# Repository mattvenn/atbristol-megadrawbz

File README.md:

# @bristol energy drawing robot

## updates

* [youtube playlist](https://www.youtube.com/playlist?list=PLmcDgdDpcaPiOdnMplbk7o1K5Kpvp_UAL)
* [photos](https://goo.gl/photos/KGhmjEyrZScbemvW7)

## details

### hardware

* [Beagle bone breakout board](hardware/bbbbbb_pcb/)
* [Pen holder](hardware/gondola_pcb/)
* [notes on stepper choice](tests/stepper-choice)

### machinekit/linuxcnc configuration

* Robot is controlled with machinekit running on a beaglebone black.
* Pen holder is controlled via Xbee radio and uses a [custom component] that runs in its own realtime thread.

* [configuration](https://github.com/mattvenn/machinekit-bipod)

### firmware

* [pen holder firmware](firmware/gondola/)

### tests

* [prototypes, tests, proof of concepts](tests)

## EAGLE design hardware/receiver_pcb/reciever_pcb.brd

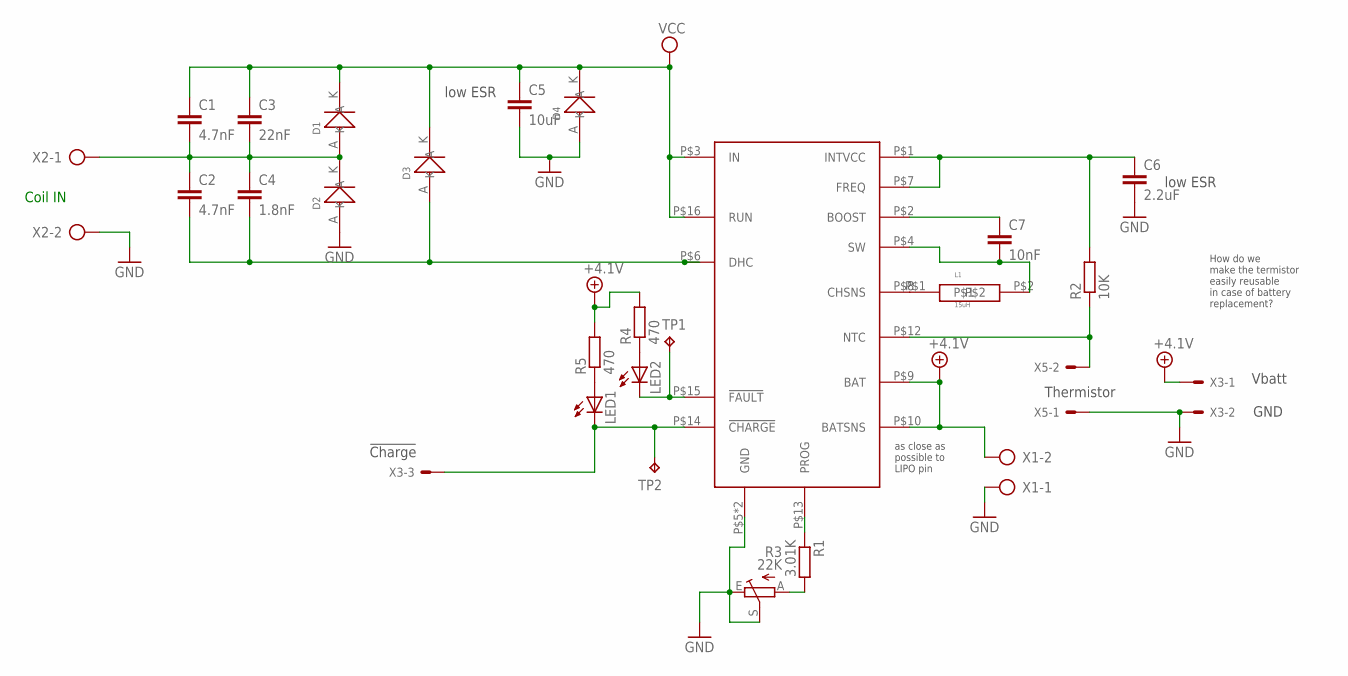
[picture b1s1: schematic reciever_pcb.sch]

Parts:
C1, C2: 4.7nF; C0805
C3: 22nF; C0805
C4: 1.8nF; C0805
C5: 10uF; C0805
C6: 2.2uF; C0805
C7: 10nF; C0805
D1, D2, D3: DFLS240L; POWERDI123
D4: 39VZ; POWERDI123
L1: 15uH; D62LCB
LED1, LED2: LEDCHIP-LED0805; CHIP-LED0805
R1: 3.01K; R0805
R2: 10K; R0805
R3: 22K; S63S
R4, R5: 470; R0805
TP1, TP2: TPTP19R; TP19R
U$1: LT4120; QFN16
X1, X2: AK500/2
X3: KK-156-3
X5: KK-156-2

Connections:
+4.1V: R4.2, R5.2, U$1.P$9 (BAT), U$1.P$10 (BATSNS), X1.2, X3.1
GND: C5.2, C6.2, D2.A, D4.A, R3.E, R3.S, U$1.P$5 (GND), U$1.P$17 (GND), X1.1, X2.2, X3.2, X5.1
unnamed: C1.2, C2.1, C3.2, C4.1, D1.A, D2.K, X2.1
unnamed: C2.2, C4.2, D3.A, U$1.P$6 (DHC)
unnamed: C6.1, R2.2, U$1.P$1 (INTVCC), U$1.P$7 (FREQ)
unnamed: C7.1, U$1.P$2 (BOOST)
unnamed: C7.2, L1.P$2, U$1.P$4 (SW)
unnamed: L1.P$1, U$1.P$8 (CHSNS)
unnamed: R1.1, U$1.P$13 (PROG)
unnamed: R2.1, U$1.P$12 (NTC), X5.2
unnamed: LED1.C, TP2.TP, U$1.P$14 (!CHARGE), X3.3
unnamed: LED2.A, R4.1
unnamed: LED1.A, R5.1
unnamed: R1.2, R3.A
unnamed: LED2.C, TP1.TP, U$1.P$15 (!FAULT)
VCC: C1.1, C3.1, C5.1, D1.K, D3.K, D4.K, U$1.P$3 (IN), U$1.P$16 (RUN)

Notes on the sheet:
Coil IN
low ESR
as close as possible to LIPO pin
How do we make the termistor easily reusable in case of battery replacement?
!Charge
Vbatt
GND
Thermistor

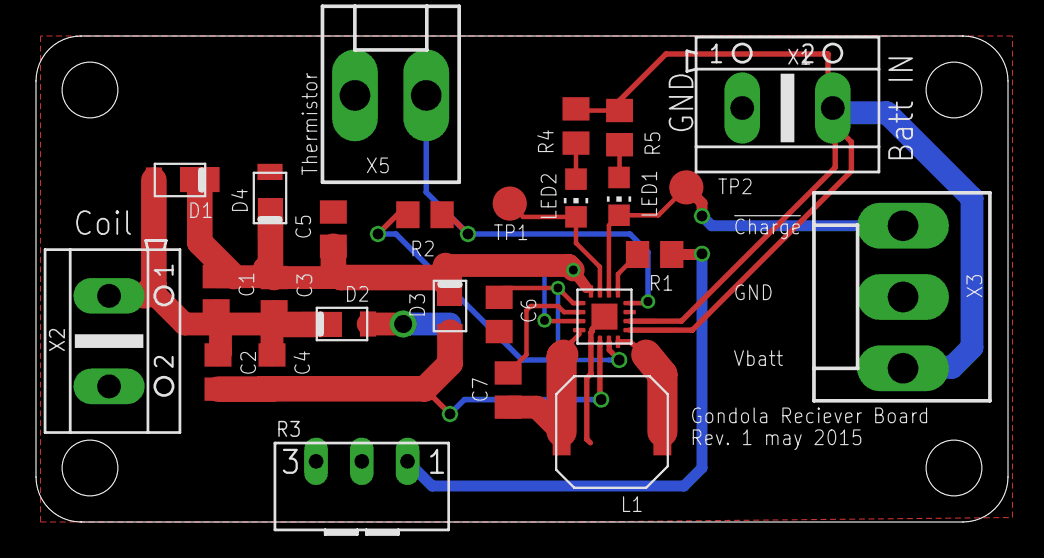
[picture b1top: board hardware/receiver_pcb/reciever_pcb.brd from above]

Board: 2 copper layers, 54.0 x 27.0 mm, 26 parts (0 on the bottom side), 16 nets.

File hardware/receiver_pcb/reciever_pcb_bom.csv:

Part,Value,Device,Package,Description,RS code,Link
C1,4.7nF,C-EUC0805,C0805,"CAPACITOR, European symbol",,
C2,4.7nF,C-EUC0805,C0805,"CAPACITOR, European symbol",,
C3,22nF,C-EUC0805,C0805,"CAPACITOR, European symbol",,
C4,1.8nF,C-EUC0805,C0805,"CAPACITOR, European symbol",,
C5,10uF,C-EUC0805,C0805,"CAPACITOR, European symbol",,
C6,2.2uF,C-EUC0805,C0805,"CAPACITOR, European symbol",,
C7,10nF,C-EUC0805,C0805,"CAPACITOR, European symbol",,
D1,DFLS240L,DFLS240L,POWERDI123,,,
D2,DFLS240L,DFLS240L,POWERDI123,,,
D3,DFLS240L,DFLS240L,POWERDI123,,,
D4,39VZ,DFLS240L,POWERDI123,,822-2497,http://uk.rs-online.com/web/p/zener-diodes/8222497/
L1,15uH,L-EUL1812,L1812,Toko coil,7521327,http://uk.rs-online.com/web/p/wire-wound-surface-mount-induc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
LED1,,LEDCHIP-LED0805,CHIP-LED0805,LED,,
LED2,,LEDCHIP-LED0805,CHIP-LED0805,LED,,
R1,3.01K,R-EU_R0805,R0805,"RESISTOR, European symbol",,
R2,10K,R-EU_R0805,R0805,"RESISTOR, European symbol",,
R4,470,R-EU_R0805,R0805,"RESISTOR, European symbol",,
R5,470,R-EU_R0805,R0805,"RESISTOR, European symbol",,
TP1,TPTP19R,TPTP19R,TP19R,Test pad,,
TP2,TPTP19R,TPTP19R,TP19R,Test pad,,
U$1,LT4120,LT4120,QFN16,,,
X1,,AK500/2,AK500/2,CONNECTOR,,
X2,,AK500/2,AK500/2,CONNECTOR,,
X3,,KK-156-3,KK-156-3,KK 156 HEADER,,
X4,,AK500/2,AK500/2,CONNECTOR,,

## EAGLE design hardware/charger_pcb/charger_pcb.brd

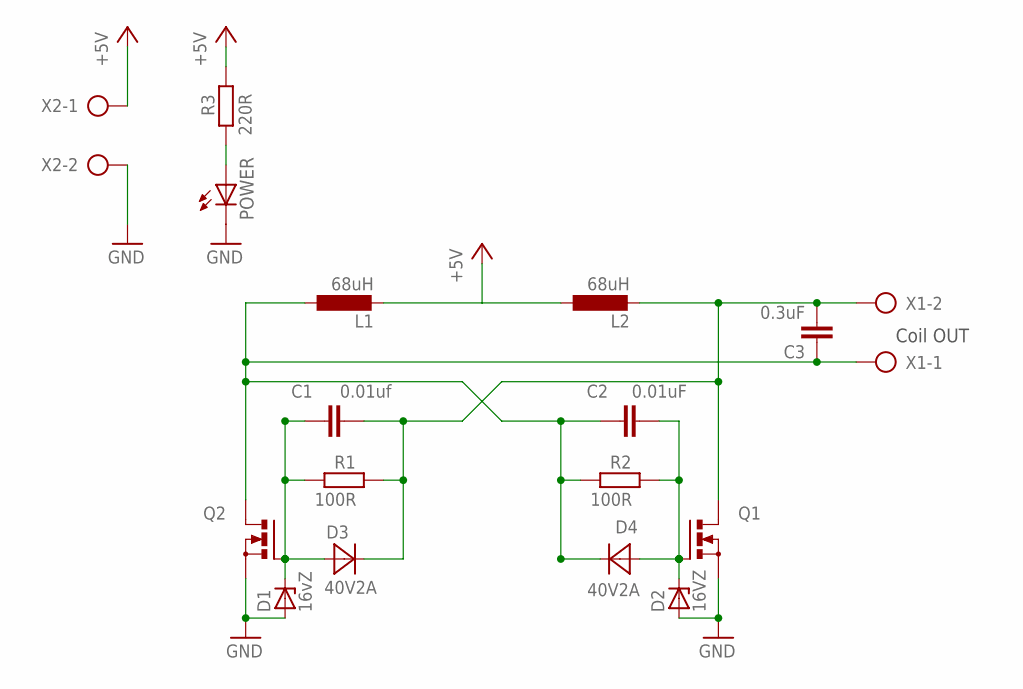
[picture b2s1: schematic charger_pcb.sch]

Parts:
C1: 0.01uf; C0805
C2: 0.01uF; C0805
C3: 0.3uF; C0805
D1: 16vZ; SOD80C
D2: 16VZ; SOD80C
D3, D4: 40V2A; SMA
L1, L2: 68uH; L5650M
POWER: LEDCHIP-LED0805; CHIP-LED0805
Q1, Q2: N-MOSFET-SO8S; SO-08
R1, R2: 100R; R0805
R3: 220R; R0805
X1, X2: AK500/2

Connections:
+5V: L1.2, L2.1, R3.2, X2.1
GND: D1.A, D2.A, POWER.C, Q1.1 (S), Q1.2 (S), Q1.3 (S), Q2.1 (S), Q2.2 (S), Q2.3 (S), X2.2
unnamed: C1.1, D1.C, D3.A, Q2.4 (G), R1.1
unnamed: C2.2, D2.C, D4.A, Q1.4 (G), R2.2
unnamed: POWER.A, R3.1
OUT1: C1.2, C3.2, D3.C, L2.2, Q1.5 (D), Q1.6 (D), Q1.7 (D), Q1.8 (D), R1.2, X1.2
OUT2: C2.1, C3.1, D4.C, L1.1, Q2.5 (D), Q2.6 (D), Q2.7 (D), Q2.8 (D), R2.1, X1.1

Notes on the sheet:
Coil OUT

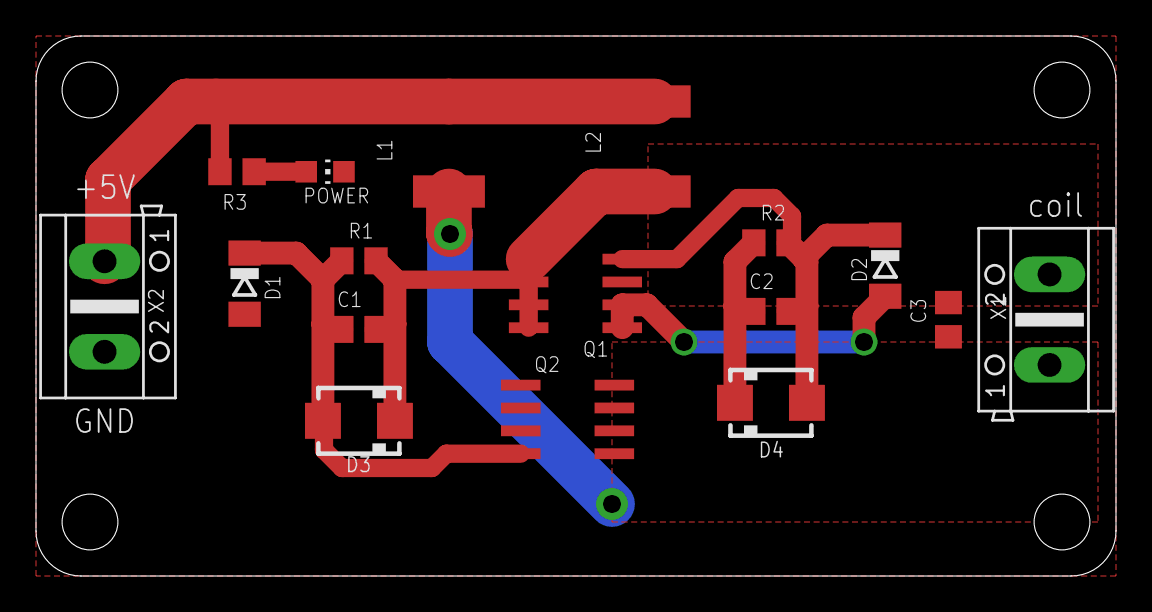
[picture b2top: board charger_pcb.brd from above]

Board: 2 copper layers, 60.0 x 30.0 mm, 17 parts (0 on the bottom side), 7 nets.

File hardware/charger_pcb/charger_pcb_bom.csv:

Qty,Value,Device,Package,Parts,Description,RS code,Link
2,,AK500/2,AK500/2,"X1, X2",CONNECTOR,2204260,http://uk.rs-online.com/web/p/pcb-terminal-blocks/2204260/
1,,LEDCHIP-LED0805,CHIP-LED0805,POWER,LED,8886057,http://uk.rs-online.com/web/p/visible-leds/8886057/
2,,N-MOSFET-SO8S,SO-08,"Q1, Q2",N-Channel MOSFET,915-4960,http://uk.rs-online.com/web/p/mosfet-transistors/9154960/
1,0.01uF,C-EUC0805,C0805,C2,"CAPACITOR, European symbol",4614013,http://uk.rs-online.com/web/p/ceramic-multilayer-capacitors/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
1,0.01uf,C-EUC0805,C0805,C1,"CAPACITOR, European symbol",4614013,http://uk.rs-online.com/web/p/ceramic-multilayer-capacitors/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
1,0.3uF,C-EUC0805,C0805,C3,"CAPACITOR, European symbol",,
2,100R,R-EU_R0805,R0805,"R1, R2","RESISTOR, European symbol",,
1,16VZ,ZENER-DIODESOD80C,SOD80C,D2,Z-Diode,7598775,http://uk.rs-online.com/web/p/zener-diodes/7598775/
1,16vZ,ZENER-DIODESOD80C,SOD80C,D1,Z-Diode,7598775,http://uk.rs-online.com/web/p/zener-diodes/7598775/
1,220R,R-EU_R0805,R0805,R3,"RESISTOR, European symbol",,
2,40V2A,MBRA340T3,SMA,"D3, D4",Surface Mount Schottky Power Rectifier,708-2337,http://uk.rs-online.com/web/p/rectifier-schottky-diodes/7082337/
2,68uH,L-EUL5650M,L5650M,"L1, L2","INDUCTOR, European symbol",6924930,http://uk.rs-online.com/web/p/wire-wound-surface-mount-induc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

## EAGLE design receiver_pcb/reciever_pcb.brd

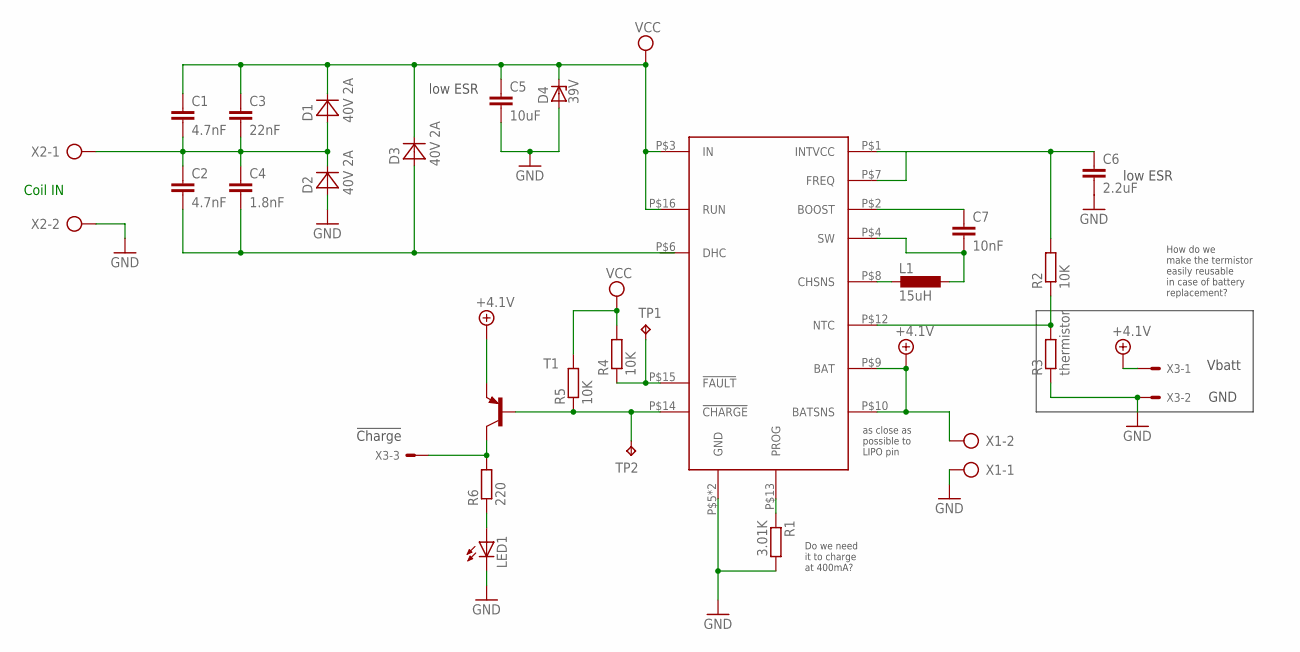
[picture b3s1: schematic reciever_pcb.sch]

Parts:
C1, C2: 4.7nF; C0805
C3: 22nF; C0805
C4: 1.8nF; C0805
C5: 10uF; C0805
C6: 2.2uF; C0805
C7: 10nF; C0805
D1, D2, D3: 40V 2A; SMA
D4: 39V; SMB
L1: 15uH; L1812
LED1: LEDCHIP-LED0805; CHIP-LED0805
R1: 3.01K; R0805
R2, R4, R5: 10K; R0805
R3: thermistor; 0207/2V
R6: 220; R0805
T1: -PNP-SOT23-BCE; SOT23-BCE
TP1, TP2: TPTP19R; TP19R
U$1: LT4120; QFN16
X1, X2: AK500/2
X3: KK-156-3

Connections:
+4.1V: T1.E, U$1.P$9 (BAT), U$1.P$10 (BATSNS), X1.2, X3.1
GND: C5.2, C6.2, D2.A, D4.A, LED1.C, R1.2, R3.1, U$1.P$5 (GND), U$1.P$17 (GND), X1.1, X2.2, X3.2
unnamed: C1.2, C2.1, C3.2, C4.1, D1.A, D2.C, X2.1
unnamed: C2.2, C4.2, D3.A
unnamed: C6.1, R2.2, U$1.P$1 (INTVCC), U$1.P$7 (FREQ)
unnamed: C7.1, U$1.P$2 (BOOST)
unnamed: C7.2, L1.1, U$1.P$4 (SW)
unnamed: L1.2, U$1.P$8 (CHSNS)
unnamed: R1.1, U$1.P$13 (PROG)
unnamed: R2.1, R3.2, U$1.P$12 (NTC)
unnamed: R5.1, T1.B, TP2.TP, U$1.P$14 (!CHARGE)
unnamed: R4.1, TP1.TP, U$1.P$15 (!FAULT)
unnamed: LED1.A, R6.1
unnamed: R6.2, T1.C, X3.3
VCC: C1.1, C3.1, C5.1, D1.C, D3.C, D4.C, R4.2, R5.2, U$1.P$3 (IN), U$1.P$16 (RUN)

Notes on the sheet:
Coil IN
low ESR
as close as possible to LIPO pin
Do we need it to charge at 400mA?
How do we make the termistor easily reusable in case of battery replacement?
!Charge
Vbatt
GND

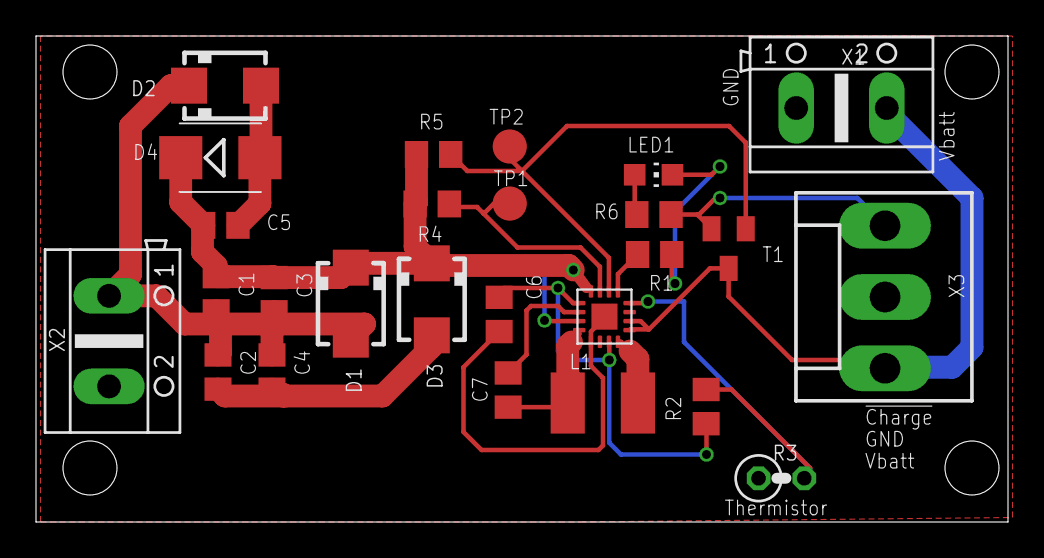
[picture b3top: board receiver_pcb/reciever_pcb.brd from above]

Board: 2 copper layers, 54.0 x 27.0 mm, 26 parts (0 on the bottom side), 15 nets.

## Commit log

2016-04-10 just turn it on
2016-04-10 fix range
2016-04-10 more testing - abandoned now
2016-04-10 supervisor config file
2016-04-10 work around broken adafruit library
2016-05-13 screwthread testing
2016-05-13 test fixture is square
2016-05-13 triangle errors!
2016-05-14 setup
2016-05-14 better res
2016-05-14 step test removed
2016-05-14 titles
2016-05-14 updated graphs
2016-05-14 clearer explanation
2016-05-14 fix bug in program that makes bad step amounts
2016-05-14 put plot back to how I expect things to work
2016-05-14 makefile
2016-05-17 dir structure
2016-05-18 wrong place
2016-05-18 preliminary schematics
2016-05-19 servo test
2016-05-19 new reciever sch
2016-05-19 1st reciever pcb
2016-05-20 emitter 1st pcb
2016-05-20 better dir struct, and some tweaks to pcbs
2016-05-23 not working
2016-05-23 first test
2016-05-23 readme
2016-05-23 more files
2016-05-23 home testing
2016-05-23 pics
2016-05-24 removed old files
2016-05-24 new graph
2016-05-24 submodule
2016-05-24 checkpoints revised with Matt, new footprints
2016-05-25 testing xbee
2016-05-25 last touches befor OSHP
2016-05-25 1mm dyneema test
2016-05-26 new tests
2016-05-26 fixed links
2016-05-31 full BOMs
2016-05-31 full BOMs again...
2016-06-01 notes
2016-06-10 slide homing
2016-06-13 test results for slider
2016-06-13 photo
2016-06-13 part number
2016-06-13 bit more intro
2016-06-13 fixed pic
2016-06-13 vid link
2016-06-13 mostly laid out
2016-06-13 first pass pcb layout
2016-06-14 footprints mostly done
2016-06-14 gondola charge
2016-06-16 stepper choices
2016-06-16 documented option
2016-06-16 silkscreen & values
2016-06-17 cap touch demo
2016-06-17 added video
2016-06-17 edit
2016-06-20 added lcd
2016-06-20 renamed
2016-06-20 gondola pcb
2016-06-22 gondola pcb to fab
2016-06-22 fixed solder mask over touch ring
2016-06-24 oshpark fab
2016-06-28 temp sense
2016-06-28 ignore
2016-06-28 cksum not working
2016-06-28 param
2016-06-29 working ok at 25ms, hal ok
2016-06-29 fixed cksum, better pin names
2016-06-30 deal with too many bytes
2016-06-30 removed old submodule
2016-06-30 moved can to gondola
2016-06-30 added new submodule
2016-06-30 typo
2016-06-30 link
2016-06-30 test canges
2016-06-30 data files
2016-06-30 rename
2016-06-30 stepper choice
2016-06-30 xbee lib
2016-06-30 libs
2016-06-30 moved to machinekit config repo
2016-06-30 test
2016-06-30 deleting xbee stuff
2016-06-30 count rx packets
2016-07-01 test xbee
2016-07-01 test probably duplicate of that in the machinekit repo
2016-07-02 gondola monitoring
2016-07-02 fix debug print
2016-07-05 added touch sense
2016-07-09 got pwm working by using /sys
2016-07-09 get rid of swserial as it causes servo jitter
2016-07-09 delay necessary to get adc flushed
2016-07-12 missing r values
2016-07-12 netlist
2016-07-12 fixed cap val
2016-07-12 test all pins
2016-07-13 tcn75 temp
2016-07-15 fixed stupid serial comms error, added charge flag
2016-07-18 pattern ideas
2016-07-23 constants
2016-07-24 sunny webbox
2016-07-27 freeboard dashboard
2016-07-28 show energy on the big digits
2016-08-01 mirror test
2016-08-01 tested local
2016-08-01 track error
2016-08-01 code for the big digits
2016-08-01 accidentally added all the files
2016-08-01 gitignore
2016-08-02 crontab
2016-08-29 submodule updates
2016-09-01 schematic
2016-09-08 battery usage pic
2016-09-09 turn off servo when charging
2016-09-09 code for enabling servo
2016-09-19 removed unused adctouch lib
2016-09-19 gondola pic
2016-10-04 notes on charger chip
2016-10-04 xbee config
2016-10-19 sleep on xbee pin, dont boot till voltage is >3500mv
2016-10-19 added @bristol config
2016-10-19 info about xbee programming
2016-10-20 found random power down issue
2016-10-24 gondola charger addon board
2016-10-24 just start up
2016-10-25 return a reply even in the event of a broken cksum
2016-10-26 start byte
2016-10-27 mcp73832 and extra hole
2016-10-27 final version
2016-11-02 low power test
2016-11-07 gondola fix notes
2016-11-07 image fix
2016-11-07 magnet idea
2016-11-17 firmware for November fix
2016-11-17 bipod for November fix
2017-06-30 root crontab
2017-07-02 new energy key
2017-07-02 fix log
2017-07-03 blanket exception handling
